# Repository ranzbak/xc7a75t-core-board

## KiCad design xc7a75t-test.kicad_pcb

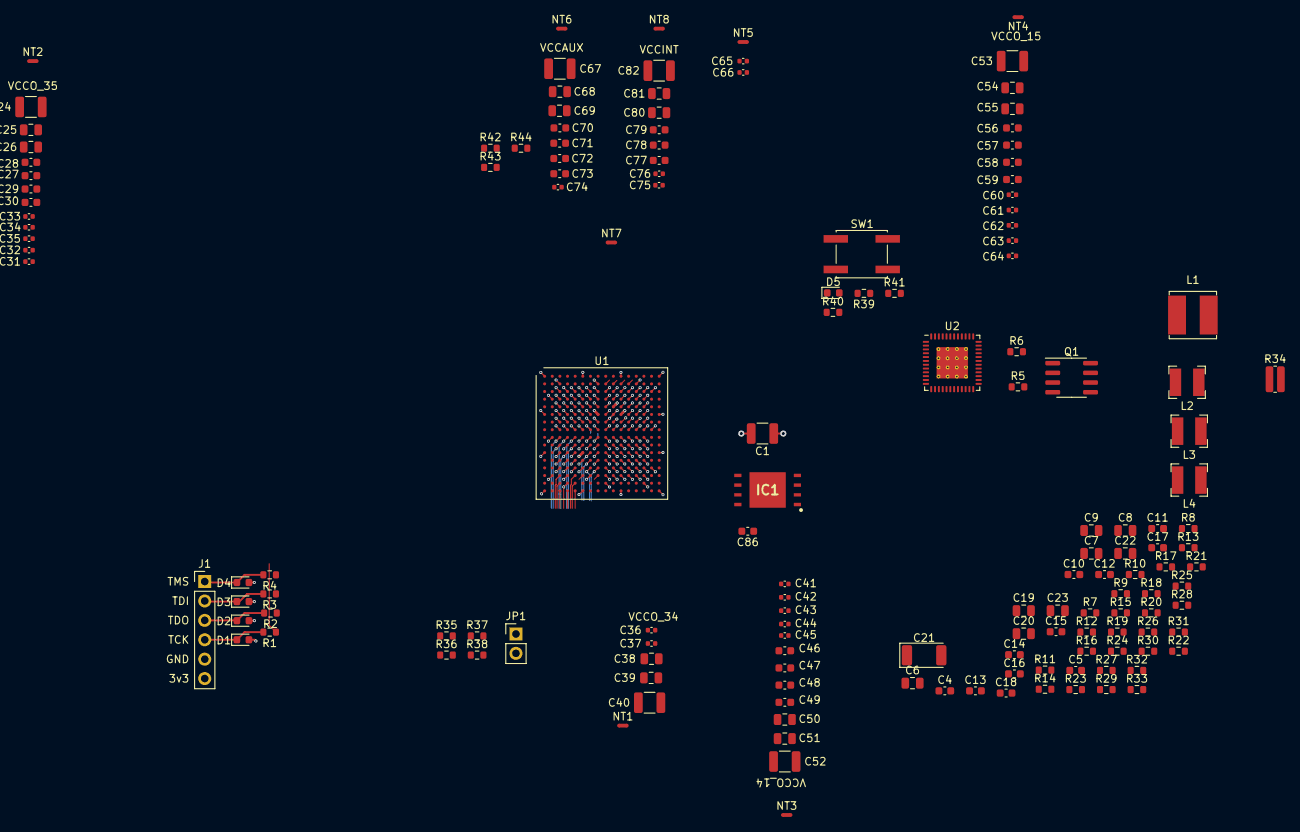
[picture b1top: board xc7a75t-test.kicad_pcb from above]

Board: 6 copper layers, 154 parts (0 on the bottom side), 70 nets.

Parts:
C1, C67, C82: 47uF; C_1210_3225Metric
C2: 0.47uF; C_0402_1005Metric
C3, C31, C32, C33, C36, C37, C43, C44, C45, C60, C61, C62, C65, C66, C74, C75, C76, C84: 47nF; C_0402_1005Metric
C4, C5, C16, C17, C86: 100nF; C_0603_1608Metric
C6, C7, C8, C9, C19: 10uF; C_0805_2012Metric
C10, C15, C18: 1uF; C_0603_1608Metric
C11: 2.7nF; C_0603_1608Metric
C12: 5.6nF; C_0603_1608Metric
C13, C14: 1.8nF; C_0603_1608Metric
C20, C22, C23: 22uF; C_0805_2012Metric
C21: 100uF; D_2010_5025Metric
C24, C40, C52, C53: 100uF; C_1210_3225Metric
C25, C26, C38, C39, C50, C51, C54, C55, C68, C69, C80, C81: 4.7uF; C_0805_2012Metric
C27, C28, C29, C30, C46, C47, C48, C49, C56, C57, C58, C59, C70, C71, C72, C73, C77, C78, C79: 470nF; C_0603_1608Metric
C34, C35, C41, C42, C63, C64, C83: 10nF; C_0402_1005Metric
C85: 100nF; C_0402_1005Metric
D1, D2, D3, D4: D_Zener_Small; D_0603_1608Metric
D5: LED_Small; LED_0603_1608Metric
IC1: IS25LP256D-JLLE; SON127P800X600X80-9N-D
J1: jtag_header_01x06; PinHeader_1x06_P2.54mm_Vertical
JP1: Jumper; PinHeader_1x02_P2.54mm_Vertical
L1: 2.2uH; L_Bourns_SRN6045TA
L2, L3, L4: 2.2uH; L_Bourns-SRN4018
NT1, NT2, NT3, NT4, NT5, NT6, NT7, NT8: Net-Tie_2; NetTie-2_SMD_Pad0.5mm
Q1: FDS9926A; SOIC-8_3.9x4.9mm_P1.27mm
R1, R2, R3, R4: 100; R_0603_1608Metric
R5, R6: 47K; R_0603_1608Metric
R7, R29: 10.2k 1%; R_0603_1608Metric
R8: 31.6k 1%; R_0603_1608Metric
R9: 7.68k 1%; R_0603_1608Metric
R10: 41.2k 1%; R_0603_1608Metric
R11: 9.53k 1% noload; R_0603_1608Metric
R12, R32: 0; R_0603_1608Metric
R13, R15, R19: 4.64k 1%; R_0603_1608Metric
R14, R16, R18, R20: 10k 1%; R_0603_1608Metric
R17: 270 1%; R_0603_1608Metric
R21: 56K2; R_0603_1608Metric
R22: 7K15; R_0603_1608Metric
R23: 9k31; R_0603_1608Metric
R24: 15k; R_0603_1608Metric
R25: 31K6 1%; R_0603_1608Metric
R26: 4.99k 1%; R_0603_1608Metric
R27: 1.91k 1%; R_0603_1608Metric
R28: 12.7k 1%; R_0603_1608Metric
R30: 7.87k 1%; R_0603_1608Metric
R31: 11.5k 1%; R_0603_1608Metric
R33: 0 noload; R_0603_1608Metric
R34: R_Shunt; R_0612_1632Metric
R35, R41: 4.7K; R_0603_1608Metric
R36: 1K; R_0603_1608Metric
R37, R38: 1k; R_0603_1608Metric
R39, R40: 300; R_0603_1608Metric
R42: 2.4k; R_0603_1608Metric
R43, R44: 4.7k; R_0603_1608Metric
SW1: SW_Push; SW_SPST_EVQQ2
U1: XC7A75T-FTG256; Xilinx_FTG256
U2: ADP5052ACPZ-R7; LFCSP-48-1EP_7x7mm_P0.5mm_EP4.1x4.1mm_ThermalVias

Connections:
+1V8: C19.1, L3.2, R19.1, R28.1
+3V3: C21.1, C86.2, IC1.8, J1.6, L1.2, NT1.1, NT2.1, NT3.1, NT4.1, NT5.1, NT6.1, NT7.1, NT8.1, R8.1, R35.1, R36.1, R38.1, R39.1, R41.1
+5V: C6.1, C7.1, C8.1, C9.1, U2.4, U2.8, U2.9, U2.23, U2.24, U2.25, U2.35, U2.36
/sheet60847A1B/JTAG_TCK_O: R1.1, U1.L7
/sheet60847A1B/JTAG_TDI_O: R3.1, U1.N7
/sheet60847A1B/JTAG_TDO_O: R2.1, U1.N8
/sheet60847A1B/JTAG_TMS_O: R4.1, U1.M7
DONE_0: R39.2, R40.1, U1.H10
GND: C1.1, C2.1, C3.1, C6.2, C7.2, C8.2, C9.2, C10.2, C11.2, C12.2, C13.2, C14.2, C15.2, C18.2, C19.2, C20.2, C21.2, C22.2, C23.2, C24.2, C25.2, C26.2, C27.2, C28.1, C29.2, C30.2, C31.2, C32.2, C33.2, C34.2, C35.2, C36.2, C37.2, C38.2, C39.2, C40.2, C41.2, C42.2, C43.2, C44.2, C45.2, C46.2, C47.2, C48.2, C49.2, C50.2, C51.2, C52.2, C53.2, C54.2, C55.2, C56.2, C57.2, C58.2, C59.2, C60.2, C61.2, C62.2, C63.2, C64.2, C65.1, C66.1, C86.1, D1.2, D2.2, D3.2, D4.2, D5.1, IC1.4, IC1.9, J1.5, JP1.2, Q1.1, Q1.3, R5.1, R6.1, R7.1, R10.1, R12.2, R14.2, R16.2, R18.2, R20.2, R25.1, R27.1, R29.1, R31.1, R33.1, R37.1, SW1.2, U1.A1, U1.A11, U1.B8, U1.C5, U1.C15, U1.D2, U1.D12, U1.E9, U1.F6, U1.F8, U1.F10, U1.F16, U1.G3, U1.G9, U1.G13, U1.H6, U1.J9, U1.J11, U1.K4, U1.K6, U1.K7, U1.K8, U1.K14, U1.L1, U1.L11, U1.M8, U1.N5, U1.N15, U1.P2, U1.P12, U1.R9, U1.T6, U1.T16, U2.2, U2.11, U2.13, U2.17, U2.18, U2.19, U2.30, U2.49
MODE_2: JP1.1, R38.2
unnamed: C4.1, U2.28
unnamed: C4.2, L2.1, Q1.5, Q1.6, U2.26, U2.27
unnamed: C5.1, U2.32
unnamed: C5.2, L1.1, Q1.7, Q1.8, U2.33, U2.34
unnamed: C11.1, R21.2
unnamed: C12.1, R22.2
unnamed: C13.1, R23.2
unnamed: C14.1, R24.2
unnamed: C15.1, U2.42
unnamed: C16.1, L3.1, U2.1
unnamed: C16.2, U2.3
unnamed: C17.1, L4.1, U2.12
unnamed: C17.2, U2.10
unnamed: C67.2, C68.2, C69.2, C70.2, C71.2, C72.2, C73.2, C74.2
unnamed: C75.2, C76.2, C77.2, C78.2, C79.2, C80.2, C81.2, C82.2
unnamed: D1.1, J1.4, R1.2
unnamed: D2.1, J1.3, R2.2
unnamed: D3.1, J1.2, R3.2
unnamed: D4.1, J1.1, R4.2
unnamed: D5.2, R40.2
unnamed: Q1.2, R5.2, U2.31
unnamed: Q1.4, R6.2, U2.29
unnamed: R7.2, R8.2, U2.40
unnamed: R9.2, R10.2, U2.21
unnamed: R11.2, R12.1, U2.38
unnamed: R13.2, R14.1, U2.47
unnamed: R15.2, R16.1, U2.5, U2.37
unnamed: R17.2, R18.1, U2.48
unnamed: R19.2, R20.1, U2.14
unnamed: R21.1, U2.39
unnamed: R22.1, U2.22
unnamed: R23.1, U2.46
unnamed: R24.1, U2.15
unnamed: R25.2, U2.41
unnamed: R26.2, R27.2, U2.6
unnamed: R28.2, R29.2, U2.45
unnamed: R30.2, R31.2, U2.16
unnamed: R32.2, R33.2, U2.43
unnamed: R35.2, U1.E7
PROGRAM_B_0: R41.2, SW1.1, U1.L9
QSPI_DQ1: IC1.2, U1.J14
QSPI_DQ2: IC1.3, R43.2, U1.K15
QSPI_DQ3: IC1.7, R44.2, U1.K16
QSPI_FCS: IC1.1, R42.2, U1.L12
QSPI_SCK: IC1.6, U1.E8
QSPI_SI: IC1.5, U1.J13
SNS0V95+: C22.1, C23.1, L2.2, R9.1, R34.1
SNS0V95-: C10.1, C18.1, C20.1, L4.2, R11.1, R13.1, R15.1, R17.1, R26.1, R30.1, R32.1, R34.2, U2.7, U2.44
VCCAUX: C67.1, C68.1, C69.1, C70.1, C71.1, C72.1, C73.1, C74.1, NT6.2, U1.G10, U1.J10, U1.K11, U1.L10
VCCBRAM: C1.2, C2.2, C3.2, NT7.2, U1.E10, U1.F11
VCCINT: C75.1, C76.1, C77.1, C78.1, C79.1, C80.1, C81.1, C82.1, NT8.2, U1.F7, U1.F9, U1.G6, U1.H9, U1.J6, U1.K9, U1.L8
VCCO_0: C65.2, C66.2, NT5.2, R42.1, R43.1, R44.1, U1.L6
VCCO_14: C41.1, C42.1, C43.1, C44.1, C45.1, C46.1, C47.1, C48.1, C49.1, C50.1, C51.1, C52.1, NT3.2, U1.L16, U1.M13, U1.N10, U1.P7, U1.R14, U1.T11
VCCO_15: C53.1, C54.1, C55.1, C56.1, C57.1, C58.1, C59.1, C60.1, C61.1, C62.1, C63.1, C64.1, NT4.2, U1.A16, U1.B13, U1.C10, U1.E14, U1.H15, U1.J12
VCCO_34: C36.1, C37.1, C38.1, C39.1, C40.1, NT1.2, U1.M3, U1.R4, U1.T1
VCCO_35: C24.1, C25.1, C26.1, C27.1, C28.2, C29.1, C30.1, C31.1, C32.1, C33.1, C34.1, C35.1, NT2.2, U1.A6, U1.B3, U1.D7, U1.E4, U1.F1, U1.J2
VREFN_0: C84.1, U1.H7
VREFP_0: C84.2, U1.J8
gndadc: C83.1, C85.1, U1.G7
vccadc: C83.2, C85.2, U1.G8

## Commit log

2021-06-01 First checkin, board no where close to doing anything.
2021-06-01 Add power plane setup
2021-06-03 Add wire up for Q-SPI flash module.
